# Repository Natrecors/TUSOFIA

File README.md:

# 🎓 TUSOFIA (Technical University of Sofia)

Welcome to my university coursework repository! This repository serves as a collection of my FCST TU-Sofia assignments, projects, and practical exercises completed during my studies at the Technical University of Sofia. 

## 📁 Repository Structure

The repository is organized by subject/course name:

* **`Prakticum/`** - Practical exercises, lab work, and hands-on assignments. (Mainly exercises on cisco packet tracer)
* **`BPE/`** - Materials and code related to the course БПЕ. (C)
* **`OIP/`** - Materials and code related to the course ОИП. (Exercises on cisco packet tracer and kicad)
* **`Fizika/`** - Scripts, calculations, and lab work for Physics.
* **`VP/`** - Foundational tasks and projects from the Introduction to Programming course. (Python)

## 💻 Technologies Used
* **Python** 
* **C**
* **Cisco packet tracer**

## 🚀 Getting Started

If you want to view or run any of these projects locally on your machine, you can clone this repository using Git:

```bash
git clone [https://github.com/Natrecors/TUSOFIA.git](https://github.com/Natrecors/TUSOFIA.git)

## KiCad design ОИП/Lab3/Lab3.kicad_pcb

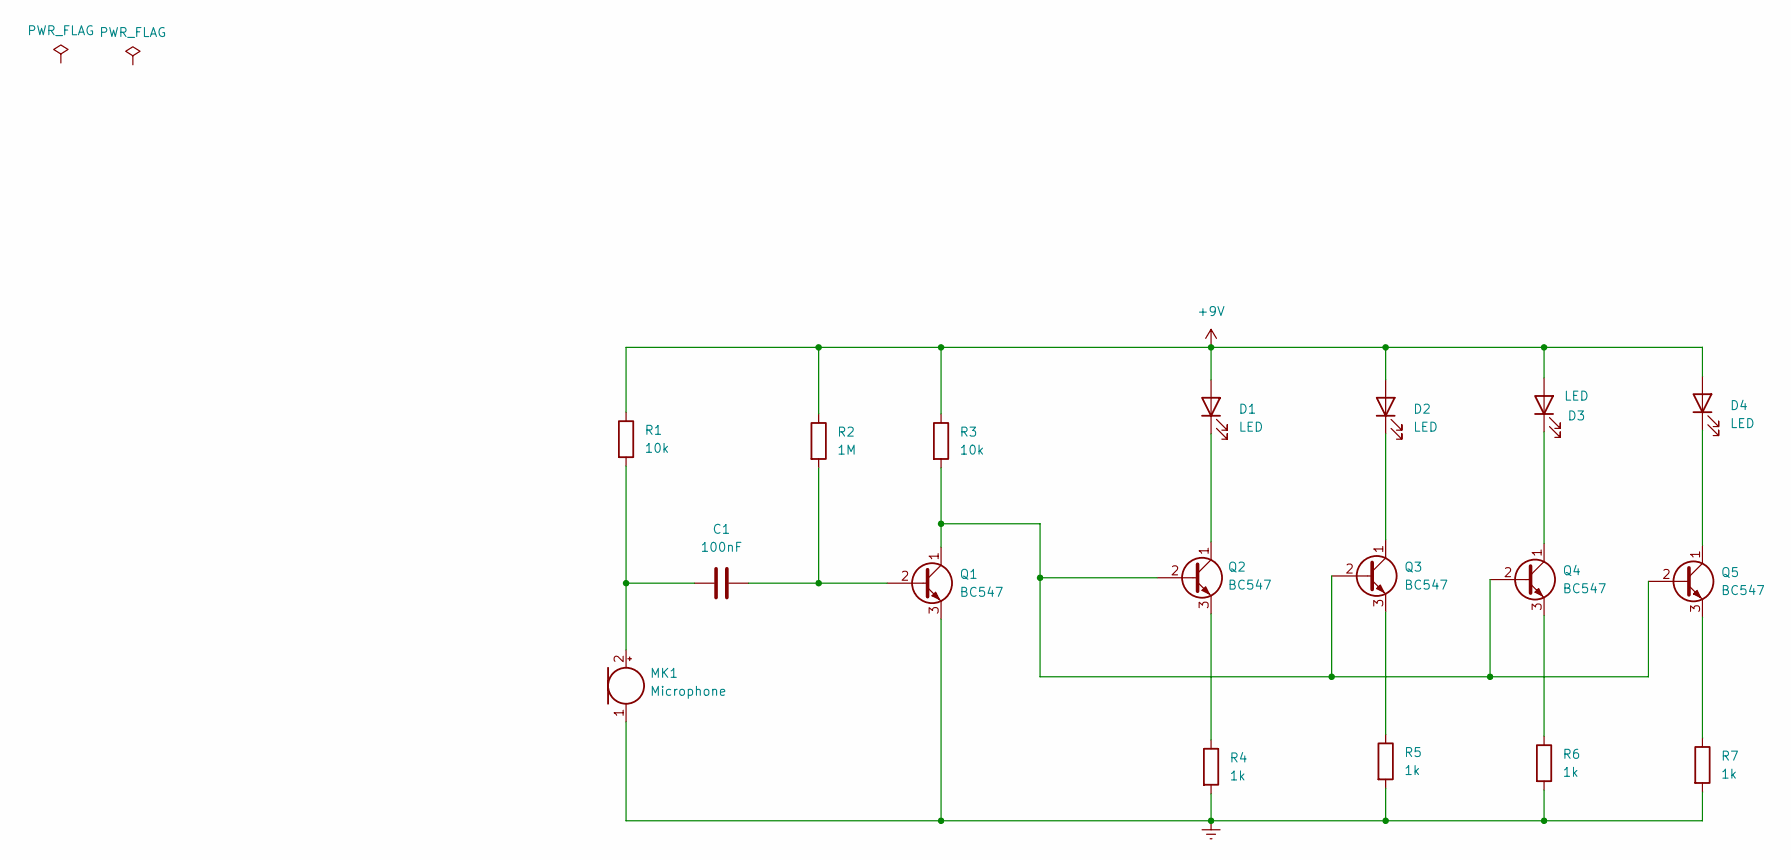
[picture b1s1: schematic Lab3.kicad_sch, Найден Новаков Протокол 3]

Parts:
C1: 100nF; C_1210_3225Metric
D1, D2, D3, D4: LED; LED_D8.0mm
MK1: Microphone; CUI_CMC-4013-SMT
Q1, Q2, Q3, Q4, Q5: BC547; TO-92_Inline
R1, R3: 10k; R_1210_3225Metric
R2: 1M; R_1210_3225Metric
R4, R5, R6, R7: 1k; R_1210_3225Metric

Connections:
+9V: D1.2 (A), D2.2 (A), D3.2 (A), D4.2 (A), R1.1, R2.1, R3.1
Earth: MK1.1 (-), Q1.3 (E), R4.2, R5.2, R6.2, R7.2
unnamed: C1.1, MK1.2 (+), R1.2
unnamed: C1.2, Q1.2 (B), R2.2
unnamed: D1.1 (K), Q2.1 (C)
unnamed: D2.1 (K), Q3.1 (C)
unnamed: D3.1 (K), Q4.1 (C)
unnamed: D4.1 (K), Q5.1 (C)
unnamed: Q1.1 (C), Q2.2 (B), Q3.2 (B), Q4.2 (B), Q5.2 (B), R3.2
unnamed: Q2.3 (E), R4.1
unnamed: Q3.3 (E), R5.1
unnamed: Q4.3 (E), R6.1
unnamed: Q5.3 (E), R7.1

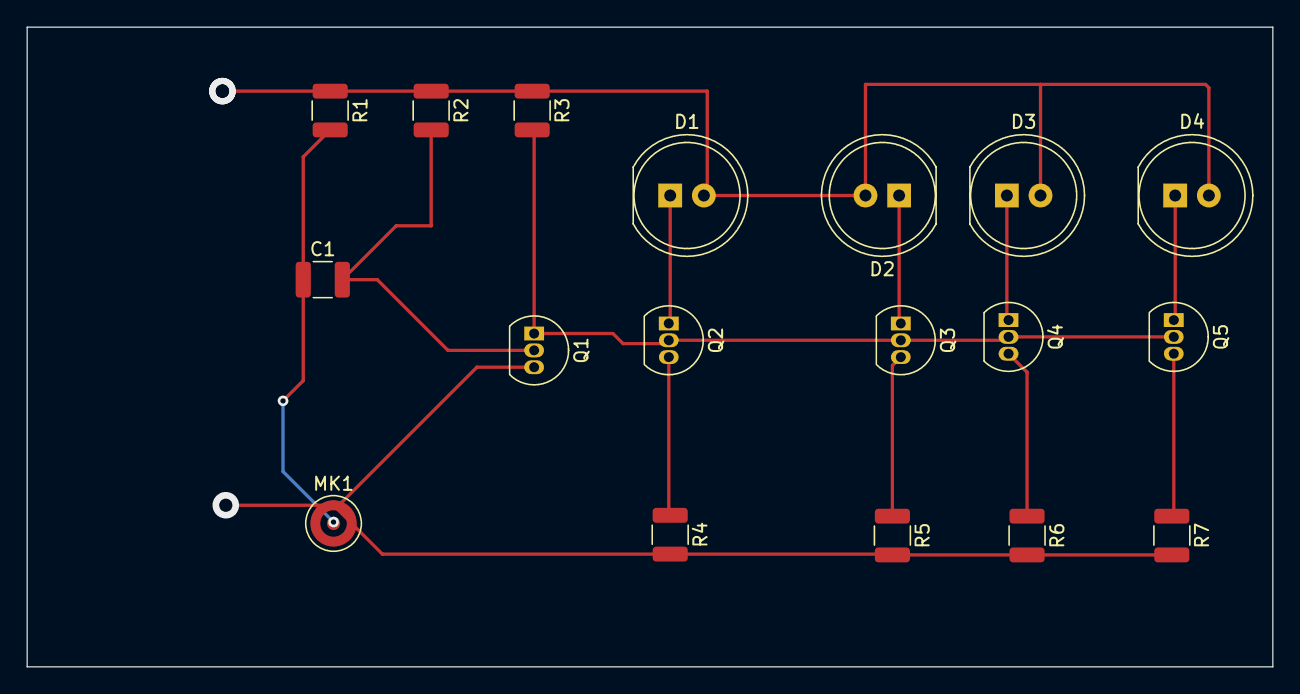
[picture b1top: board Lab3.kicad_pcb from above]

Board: 2 copper layers, 94.0 x 48.3 mm, 18 parts (0 on the bottom side), 13 nets.

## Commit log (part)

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2026-03-16 add files
2026-03-16 remove folder
2026-03-16 Add README.md for coursework repository
2026-03-17 udpdate
2026-03-17 Clarify FKST in repository description and fix casing
    Updated the README to specify FKST and correct capitalization.
2026-03-24 Update repository description for consistency
2026-03-24 BIG UPDATE(folders,files)
2026-03-26 add files drom 26.03
2026-03-26 fixing repositority
2026-03-26 fixingg
2026-03-26 Fix nested git repository and properly track SU files
2026-03-27 Add new BPE VP file and removing text output files
2026-04-09 new file adds
2026-04-09 Update course names and structure in README
2026-04-23 add Weekly files
